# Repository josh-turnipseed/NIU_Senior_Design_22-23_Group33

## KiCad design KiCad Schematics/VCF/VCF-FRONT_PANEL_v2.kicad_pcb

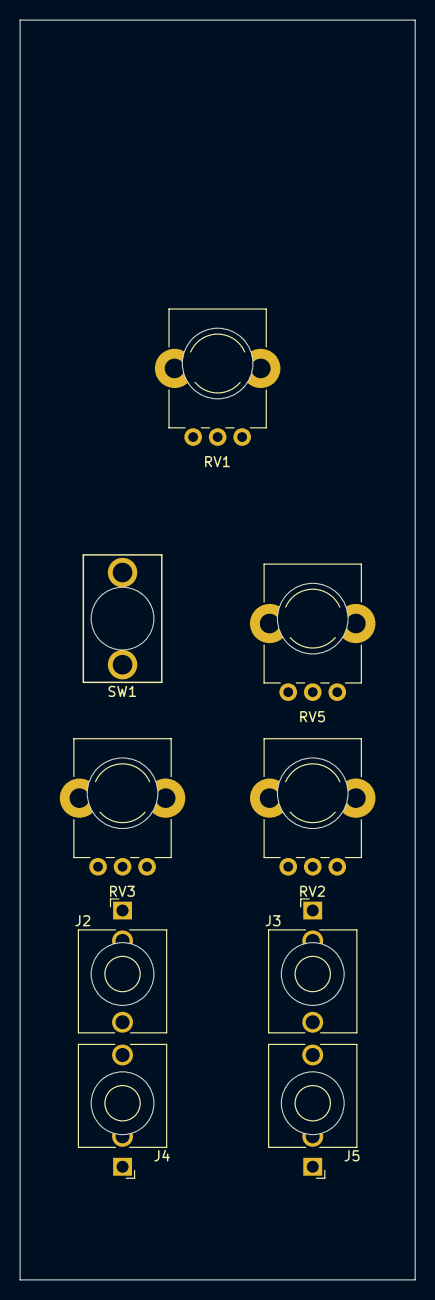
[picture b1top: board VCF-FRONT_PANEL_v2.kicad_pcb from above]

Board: 2 copper layers, 40.3 x 128.5 mm, 13 parts (0 on the bottom side), 4 nets, no tracks yet.

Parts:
J2: CV2; Jack_3.5mm_QingPu_WQP-PJ398SM_Vertical_CircularHoles
J3: CV1; Jack_3.5mm_QingPu_WQP-PJ398SM_Vertical_CircularHoles
J4: IN; Jack_3.5mm_QingPu_WQP-PJ398SM_Vertical_CircularHoles
J5: OUT; Jack_3.5mm_QingPu_WQP-PJ398SM_Vertical_CircularHoles
RV1: 50k; Alpha_9mm_Potentiometer_Aligned
RV2, RV3, RV5: 100k; Alpha_9mm_Potentiometer_Aligned
Ref**: Subminiature_Switch; Sub_Miniature_Switch_MountingHole_3.5mm
Ref**#2, Ref**#3, Ref**#4: Subminiature_Switch; Sub_Miniature_Switch_MountingHole_3.5mm
SW1: SW_SPDT; SPDT toggle on-off-on

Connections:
/CV1: J3.T, RV2.3
/CV2: J2.T, RV3.3
/OUT: J5.T, SW1.2 (B)
GND1: J2.S, J2.TN, J3.S, J3.TN, J4.S, J4.TN, J5.S, RV2.1, RV3.1, RV5.1

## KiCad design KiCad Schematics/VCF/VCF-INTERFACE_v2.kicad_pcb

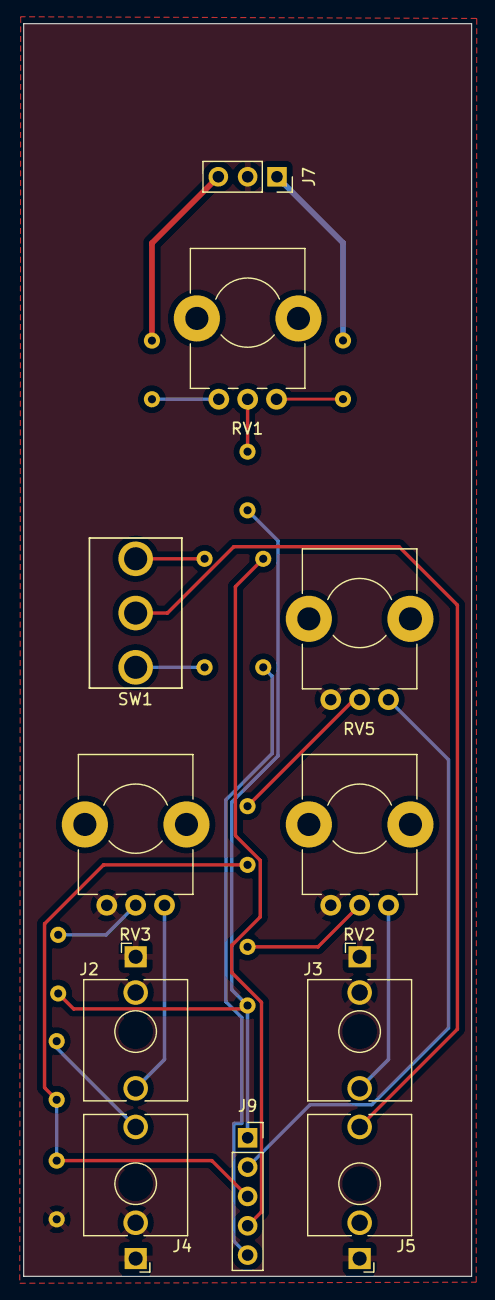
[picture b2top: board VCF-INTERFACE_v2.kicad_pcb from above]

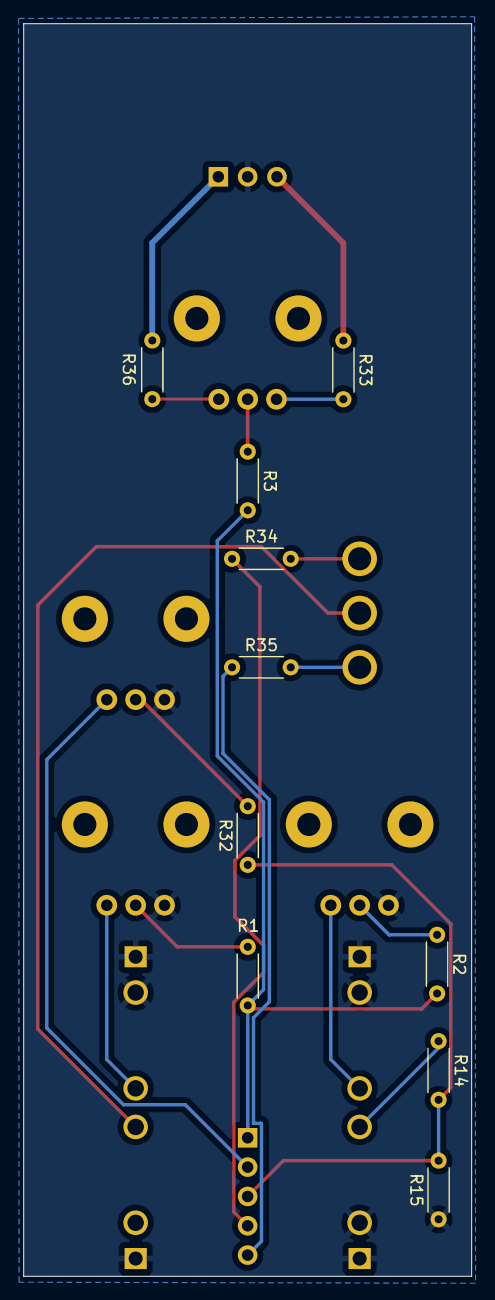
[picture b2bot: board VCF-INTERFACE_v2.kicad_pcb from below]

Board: 2 copper layers, 38.8 x 108.5 mm, 21 parts (10 on the bottom side), 20 nets.

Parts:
J2: CV2; Jack_3.5mm_QingPu_WQP-PJ398SM_Vertical_CircularHoles
J3: CV1; Jack_3.5mm_QingPu_WQP-PJ398SM_Vertical_CircularHoles
J4: IN; Jack_3.5mm_QingPu_WQP-PJ398SM_Vertical_CircularHoles
J5: OUT; Jack_3.5mm_QingPu_WQP-PJ398SM_Vertical_CircularHoles
J7: Inter1; PinSocket_1x03_P2.54mm_Vertical
J9: Inter2; PinSocket_1x05_P2.54mm_Vertical
R1, R2, R3, R14: 100k; R_Axial_DIN0204_L3.6mm_D1.6mm_P5.08mm_Horizontal
R15, R34, R35: 1k; R_Axial_DIN0204_L3.6mm_D1.6mm_P5.08mm_Horizontal
R32: 220k; R_Axial_DIN0204_L3.6mm_D1.6mm_P5.08mm_Horizontal
R33, R36: 27k; R_Axial_DIN0204_L3.6mm_D1.6mm_P5.08mm_Horizontal
RV1: 50k; Alpha_9mm_Potentiometer_Aligned
RV2, RV3, RV5: 100k; Alpha_9mm_Potentiometer_Aligned
SW1: SW_SPDT; SPDT toggle on-off-on

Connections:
+12VA: J7.1, R36.2
-12VA: J7.3, R33.1
/12out: R34.2, SW1.3 (C)
/24out: R35.2, SW1.1 (A)
/CF_V: R3.1, RV1.2
/CV1: J3.T, RV2.3
/CV1_ATN: R1.1, RV2.2
/CV2: J2.T, RV3.3
/CV2_ATN: R2.1, RV3.2
/IN: J4.T, R14.1
/OUT: J5.T, SW1.2 (B)
/Res_ATN: R32.2, RV5.2
Audio_1st_invert_INT: J9.3, R14.2, R15.2, R32.1
Audio_-12Out_INT: J9.4, R34.1
Audio_-24Out_INT: J9.5, R35.1
CV_Sum_INT: J9.1, R1.2, R2.2, R3.2
GND1: J2.S, J2.TN, J3.S, J3.TN, J4.S, J4.TN, J5.S, J7.2, R15.1, RV2.1, RV3.1, RV5.1
unnamed: R33.2, RV1.1
unnamed: R36.1, RV1.3
Res_INT: J9.2, RV5.3

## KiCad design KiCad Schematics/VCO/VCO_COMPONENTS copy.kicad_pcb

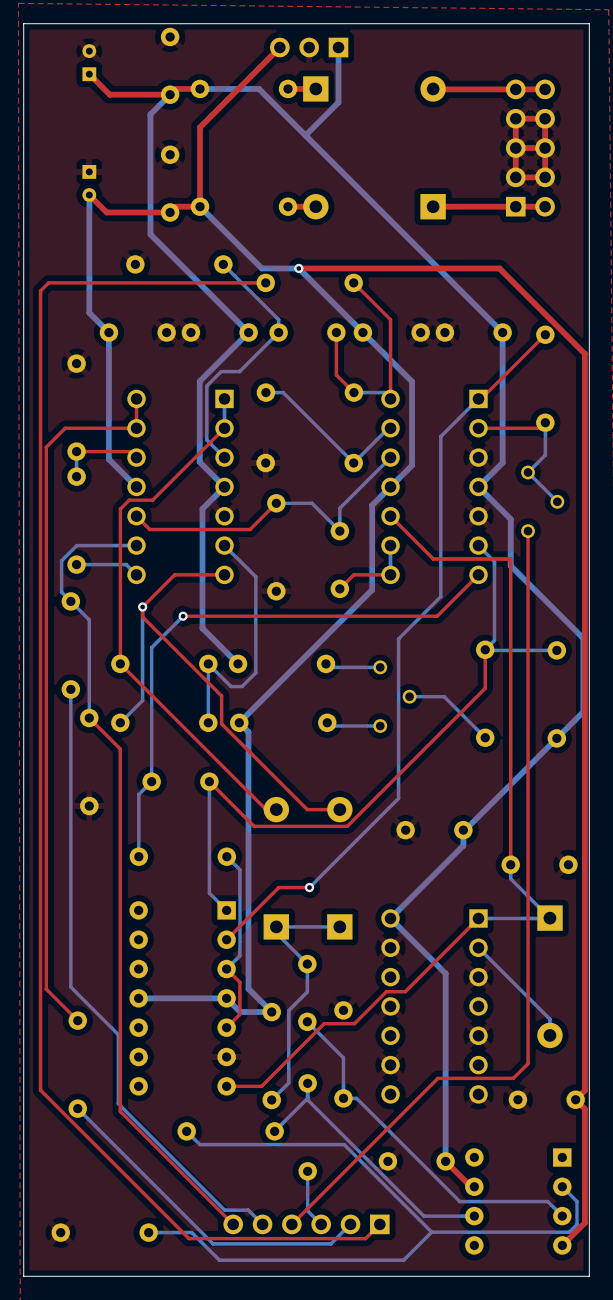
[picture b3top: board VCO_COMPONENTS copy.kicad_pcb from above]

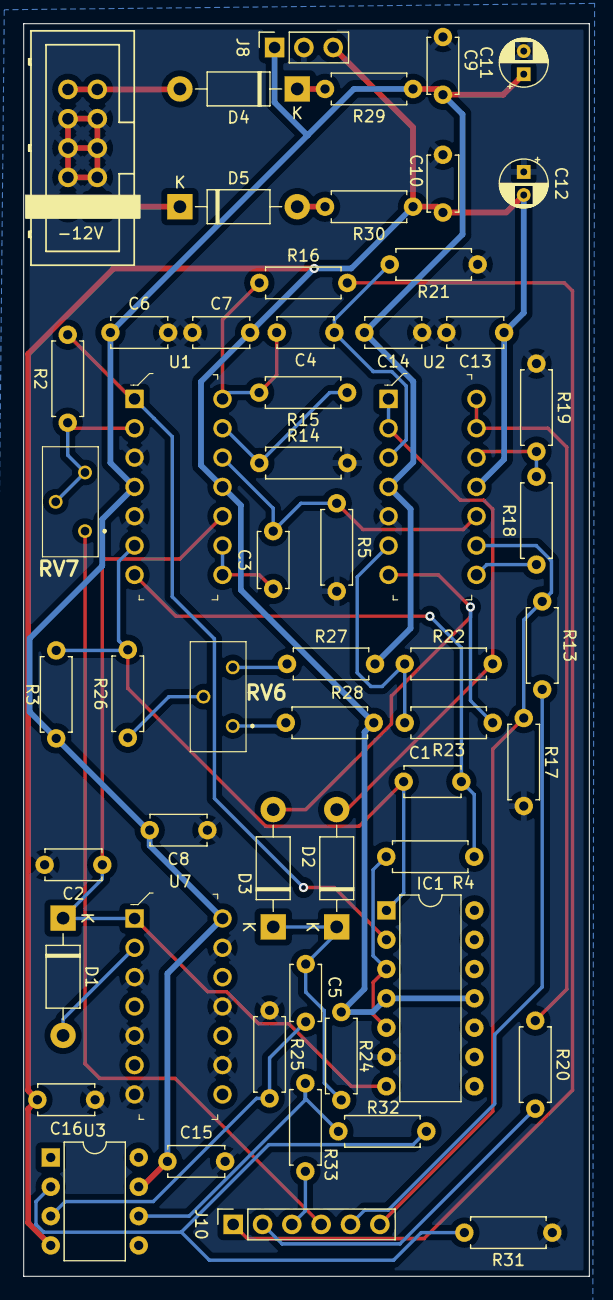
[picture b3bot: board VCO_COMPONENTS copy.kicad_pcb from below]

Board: 2 copper layers, 49.0 x 108.5 mm, 56 parts (56 on the bottom side), 38 nets.

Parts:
C1: 30p; C_Disc_D4.7mm_W2.5mm_P5.00mm
C2: 2.2n; C_Disc_D4.7mm_W2.5mm_P5.00mm
C3, C4, C5: 1u; C_Disc_D4.7mm_W2.5mm_P5.00mm
C6, C7, C8, C9, C10, C13, C14, C15, C16: 0.1u; C_Disc_D4.7mm_W2.5mm_P5.00mm
C11, C12: 4.7u; CP_Radial_D4.0mm_P2.00mm
D1, D2, D3: 1N4148; D_DO-41_SOD81_P10.16mm_Horizontal
D4, D5: 1N5819; D_DO-41_SOD81_P10.16mm_Horizontal
IC1: 300P14-U; DIP-14_W7.62mm
J1: Eurorack 10 DIP Header; Eurorack_10_pin_header
J8: Conn_01x03; PinSocket_1x03_P2.54mm_Vertical
J10: Conn_01x06; PinSocket_1x06_P2.54mm_Vertical
R2: 1.87k; R_Axial_DIN0207_L6.3mm_D2.5mm_P7.62mm_Horizontal
R3, R26: 1Meg; R_Axial_DIN0207_L6.3mm_D2.5mm_P7.62mm_Horizontal
R4: 500; R_Axial_DIN0207_L6.3mm_D2.5mm_P7.62mm_Horizontal
R5, R15, R18: 100k; R_Axial_DIN0207_L6.3mm_D2.5mm_P7.62mm_Horizontal
R13, R19: 68k; R_Axial_DIN0207_L6.3mm_D2.5mm_P7.62mm_Horizontal
R14: 47k; R_Axial_DIN0207_L6.3mm_D2.5mm_P7.62mm_Horizontal
R16, R20, R27, R28, R33: 1k; R_Axial_DIN0207_L6.3mm_D2.5mm_P7.62mm_Horizontal
R17: 14k; R_Axial_DIN0207_L6.3mm_D2.5mm_P7.62mm_Horizontal
R21, R25: 200k; R_Axial_DIN0207_L6.3mm_D2.5mm_P7.62mm_Horizontal
R22, R23, R31, R32: 10k; R_Axial_DIN0207_L6.3mm_D2.5mm_P7.62mm_Horizontal
R24: 20k; R_Axial_DIN0207_L6.3mm_D2.5mm_P7.62mm_Horizontal
R29, R30: 10; R_Axial_DIN0207_L6.3mm_D2.5mm_P7.62mm_Horizontal
RV6: 1Meg; 3296Y1502LF
RV7: 5K; 3296Y1502LF
U1, U2: TL074CN; DIP-14_W3mm
U3: TL071CP; DIP-8_W7.62mm
U7: CD40106BE; DIP-14_W3mm

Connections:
+12V: C6.1, C8.2, C9.2, C11.1, C14.2, C15.1, J8.1, R3.1, R27.2, R29.1, U1.4 (VCC), U2.4 (VCC), U3.7 (V+), U7.14 (VDD)
-12V: C7.2, C10.1, C12.2, C13.1, C16.2, IC1.4 (SUB_1), IC1.11 (SUB_2), J8.3, R24.1, R28.1, R30.1, U1.11 (GND), U2.11 (GND), U3.4 (V-)
/12+: D4.2 (A), J1.9, J1.10
/12-: D5.1 (K), J1.1, J1.2
/D+: D4.1 (K), R29.2
/D-: D5.2 (A), R30.2
/PWM_Bin: R18.2, R19.2, U2.12
/PWM_out: R18.1, U2.8
/Pulse_buff: R20.1, U2.13, U2.14
/Saw_amp1: C4.1, R15.2, R16.1, U1.14
/Saw_amp2: R14.1, R15.1, U1.13
/Saw_buff: C3.1, U1.8, U1.9
/ac_couple: C3.2, R5.1, U1.12, U2.10
/emit: IC1.3 (E1), IC1.5 (E3), R4.2
/ic1: C1.1, IC1.1 (C1), R3.2, R26.2, U1.6
/ic2: C2.1, D1.1 (K), IC1.7 (C3), U1.10, U7.1 (A)
/out_emit: C1.2, R4.1, U1.7
/scale_in: IC1.2 (B1), R2.2, U1.1
/schmitt_out: D1.2 (A), U7.2 (~A)
/tri_amp_in: R22.1, R23.2, U2.6
/tri_amp_out: D3.2 (A), R23.1, U2.7
/tri_buff: D2.2 (A), R22.2, U2.1, U2.2
/tri_in: C4.2, R21.2, U2.3
/tri_inv: R31.2, R32.2, U3.2 (-)
/tri_op_out: R32.1, R33.1, U3.6
/tri_pre: C5.2, R25.2, U3.3 (+)
/tri_sum: C5.1, D2.1 (K), D3.1 (K), R24.2
/trim+: R27.1, RV6.3
/trim-: R28.2, RV6.1
/trim_scale: R2.1, RV7.2, RV7.3, U1.2
/trim_tune: R26.1, RV6.2
AP1: J10.5, R13.2
GND: C2.2, C6.2, C7.1, C8.1, C9.1, C10.2, C11.2, C12.1, C13.2, C14.1, C15.2, C16.1, IC1.6 (B3), J1.3, J1.4, J1.5, J1.6, J1.7, J1.8, J8.2, R5.2, R14.2, R17.2, R19.1, R21.1, R25.1, R31.1, U1.3, U1.5, U2.5, U7.3 (B), U7.5 (C), U7.7 (VSS), U7.9 (D), U7.11 (E), U7.13 (F)
In_Sum1: J10.4, RV7.1
PWM_Com1: J10.6, R13.1, R17.1, U2.9
Pulse Out1: J10.2, R20.2
Saw Out1: J10.1, R16.2
Triangle Out1: J10.3, R33.2

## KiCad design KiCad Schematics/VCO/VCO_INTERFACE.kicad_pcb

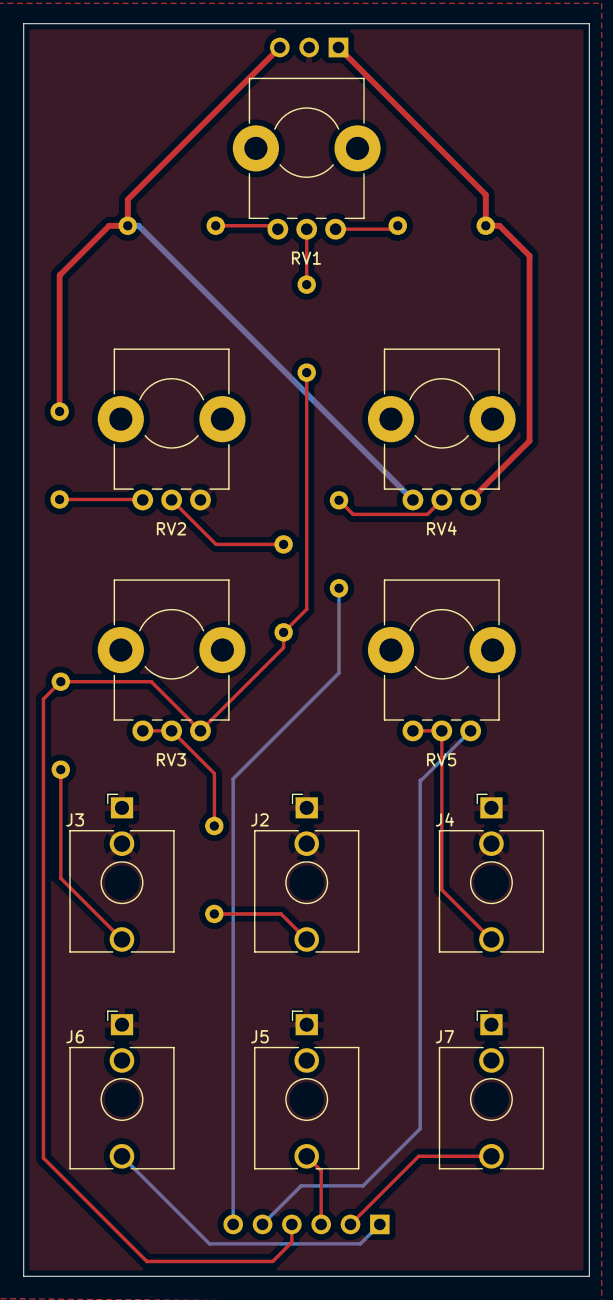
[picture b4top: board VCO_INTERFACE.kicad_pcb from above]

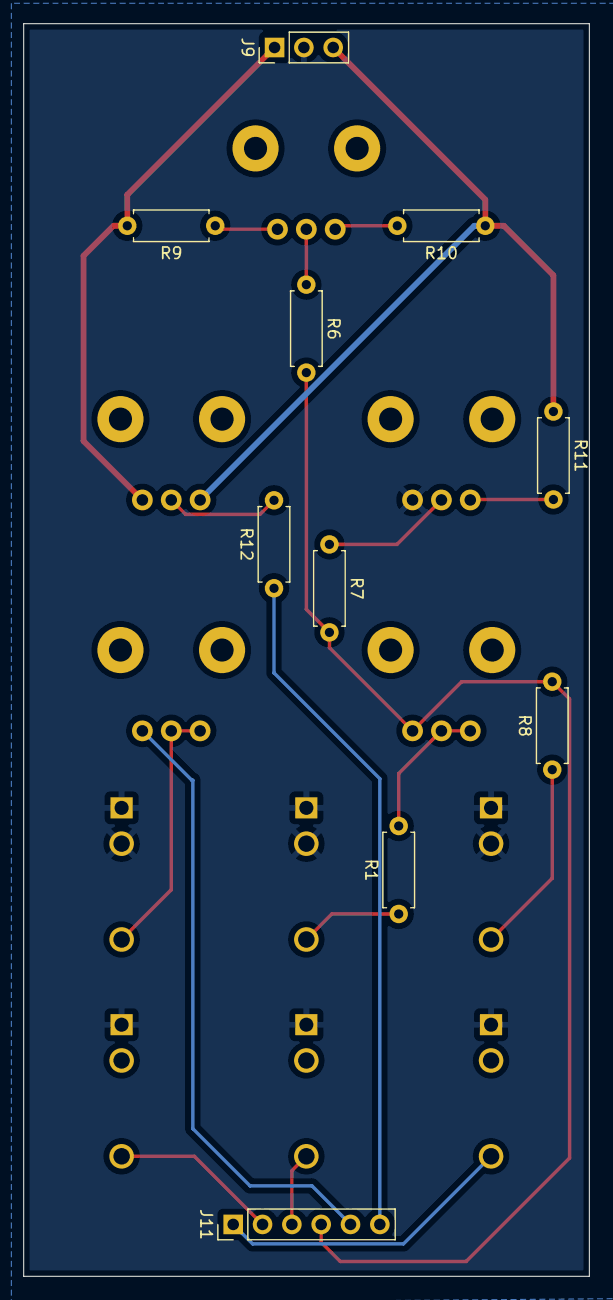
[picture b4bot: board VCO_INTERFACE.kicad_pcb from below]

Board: 2 copper layers, 49.0 x 108.5 mm, 21 parts (10 on the bottom side), 19 nets.

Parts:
J2: FM; Jack_3.5mm_QingPu_WQP-PJ398SM_Vertical_CircularHoles
J3: CV; Jack_3.5mm_QingPu_WQP-PJ398SM_Vertical_CircularHoles
J4: PWM; Jack_3.5mm_QingPu_WQP-PJ398SM_Vertical_CircularHoles
J5: Triangle; Jack_3.5mm_QingPu_WQP-PJ398SM_Vertical_CircularHoles
J6: Saw; Jack_3.5mm_QingPu_WQP-PJ398SM_Vertical_CircularHoles
J7: Pulse; Jack_3.5mm_QingPu_WQP-PJ398SM_Vertical_CircularHoles
J9: Conn_01x03; PinHeader_1x03_P2.54mm_Vertical
J11: Conn_01x06; PinHeader_1x06_P2.54mm_Vertical
R1, R6, R8, R9, R11, R12: 100k; R_Axial_DIN0207_L6.3mm_D2.5mm_P7.62mm_Horizontal
R7: 1Meg; R_Axial_DIN0207_L6.3mm_D2.5mm_P7.62mm_Horizontal
R10: 33k; R_Axial_DIN0207_L6.3mm_D2.5mm_P7.62mm_Horizontal
RV1, RV2: 100K; Alpha_9mm_Potentiometer_Aligned
RV3: 1Meg; Alpha_9mm_Potentiometer_Aligned
RV4: 100k; Alpha_9mm_Potentiometer_Aligned
RV5: 250k; Alpha_9mm_Potentiometer_Aligned

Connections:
+12VA: J9.1, R9.2, RV4.3
-12VA: J9.3, R10.1, R11.1, RV4.1
/CV_in: J3.T, R8.1
/Coarse: R6.1, RV1.2
/Coarse_div1: R9.1, RV1.3
/Coarse_div2: R10.2, RV1.1
/FM_in: J2.T, R1.1
/FM_pot: R1.2, RV3.1, RV3.2
/Fine: R7.1, RV2.2
/PWM_LP: R12.2, RV4.2
/PWM_Pot: J4.T, RV5.1, RV5.2
/fine_div: R11.2, RV2.1
AP2: J11.5, RV5.3
GND1: J2.S, J2.TN, J3.S, J3.TN, J4.S, J4.TN, J5.S, J6.S, J7.S, J9.2, RV2.3
In_Sum2: J11.4, R6.2, R7.2, R8.2, RV3.3
PWM_Com2: J11.6, R12.1
Pulse Out2: J7.T, J11.2
Saw Out2: J6.T, J11.1
Triangle Out2: J5.T, J11.3

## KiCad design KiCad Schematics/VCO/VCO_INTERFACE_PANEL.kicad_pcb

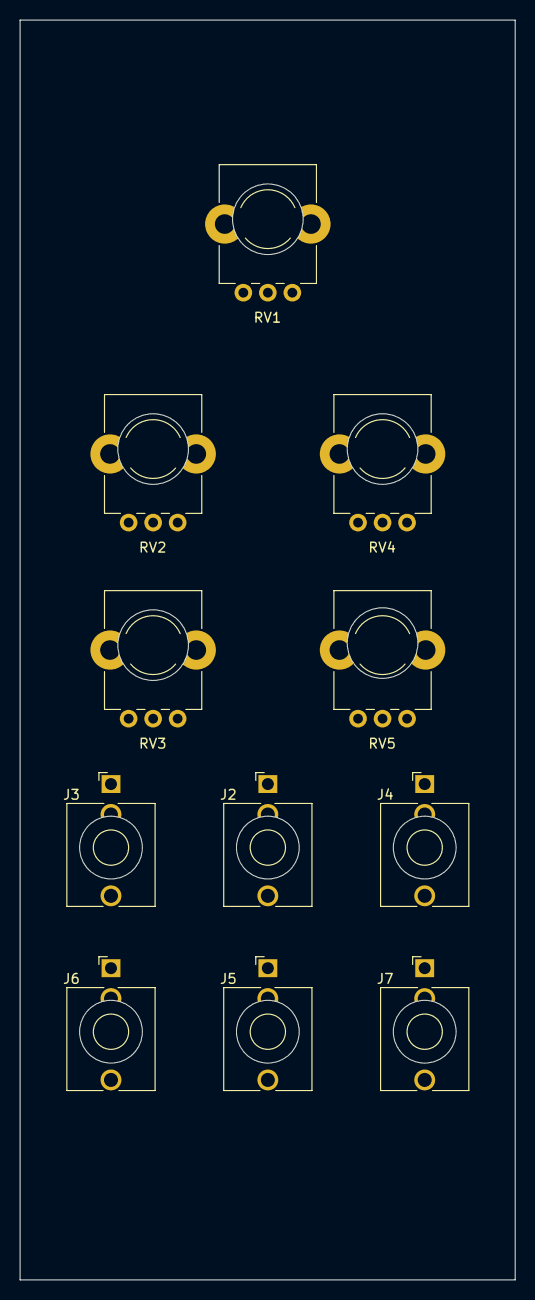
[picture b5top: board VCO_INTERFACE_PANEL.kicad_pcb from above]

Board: 2 copper layers, 50.5 x 128.5 mm, 17 parts (0 on the bottom side), 3 nets, no tracks yet.

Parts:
J2: FM; Jack_3.5mm_QingPu_WQP-PJ398SM_Vertical_CircularHoles
J3: CV; Jack_3.5mm_QingPu_WQP-PJ398SM_Vertical_CircularHoles
J4: PWM; Jack_3.5mm_QingPu_WQP-PJ398SM_Vertical_CircularHoles
J5: Triangle; Jack_3.5mm_QingPu_WQP-PJ398SM_Vertical_CircularHoles
J6: Saw; Jack_3.5mm_QingPu_WQP-PJ398SM_Vertical_CircularHoles
J7: Pulse; Jack_3.5mm_QingPu_WQP-PJ398SM_Vertical_CircularHoles
RV1, RV2: 100K; Alpha_9mm_Potentiometer_Aligned
RV3: 1Meg; Alpha_9mm_Potentiometer_Aligned
RV4: 100k; Alpha_9mm_Potentiometer_Aligned
RV5: 250k; Alpha_9mm_Potentiometer_Aligned
Ref**: Subminiature_Switch; Sub_Miniature_Switch_MountingHole_3.5mm
Ref**#2, Ref**#3, Ref**#4, Ref**#5, Ref**#6: Subminiature_Switch; Sub_Miniature_Switch_MountingHole_3.5mm

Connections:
/FM_pot: RV3.1, RV3.2
/PWM_Pot: J4.T, RV5.1, RV5.2
GND1: J2.S, J2.TN, J3.S, J3.TN, J4.S, J4.TN, J5.S, J6.S, J7.S, RV2.3
